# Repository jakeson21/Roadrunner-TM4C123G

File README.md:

# Roadrunner
Arduino clone based on TI's TM4C123G, an ARM M4F running at 80 MHz.

# Project Goal 
The goal of this project is to build a bridge between Texas Instrument's Tiva™ C LaunchPad, based on the TM4C123GH6PM, and the Arduino form factor. The LaunchPad series of development kits already benefit from an Arduino-like code development environment in the form of Energia, but lack a compatible form factor to make use of the extensive list of shields.

This project aims to merge these two worlds by putting the processing power and integrated peheripherial set of the 80-MHz ARM M4F based TM4C123 series of micro controllers into the Arduino-Leo (and Uno, Duemilanove, Due, *Mega) compatible form factor.
This will provide typical Arduino users with a much more powerful board while maintaining a familiar programming environment (through the use of Energia). It also provides a platform for those wanting to grow beyond this basic development approach into a more low-level IDE by using TI's free Code Composer Studio and selecting the EK-TM4C123GXL project configuration.

*The board breaks out all pins, but only utilizes the basic set of headers to maintain a 2" x 3" form factor.

# Other notable parameters
Most GPIO are 5V tolerant
Peripheral libraries are pre-loaded onto on-board ROM, reducing support code size.
32-bit CPU with single-precision FPU
Single-cycle multiply instruction and hardware divide
16-bit SIMD vector processing unit
Ultra-low power consumption with integrated sleep modes
etc... See datasheet for more information

# Project Planning
✔ Circuit design (using KiCAD). Programming will rely on the use of an EK-TM4C123GXL dev kit by tapping into its target ICDI JTAG headers.

✔ Board layout, including relocating Energia defined pins to their Arduino form factor locations.

✔ Fabrication (sent to OSH Park 4/16/2017)

✔ Board assembly

✔ Create custom board definition for use in Energia

▢ Hardware testing and verification

▢ Mass-production if enough people are interested

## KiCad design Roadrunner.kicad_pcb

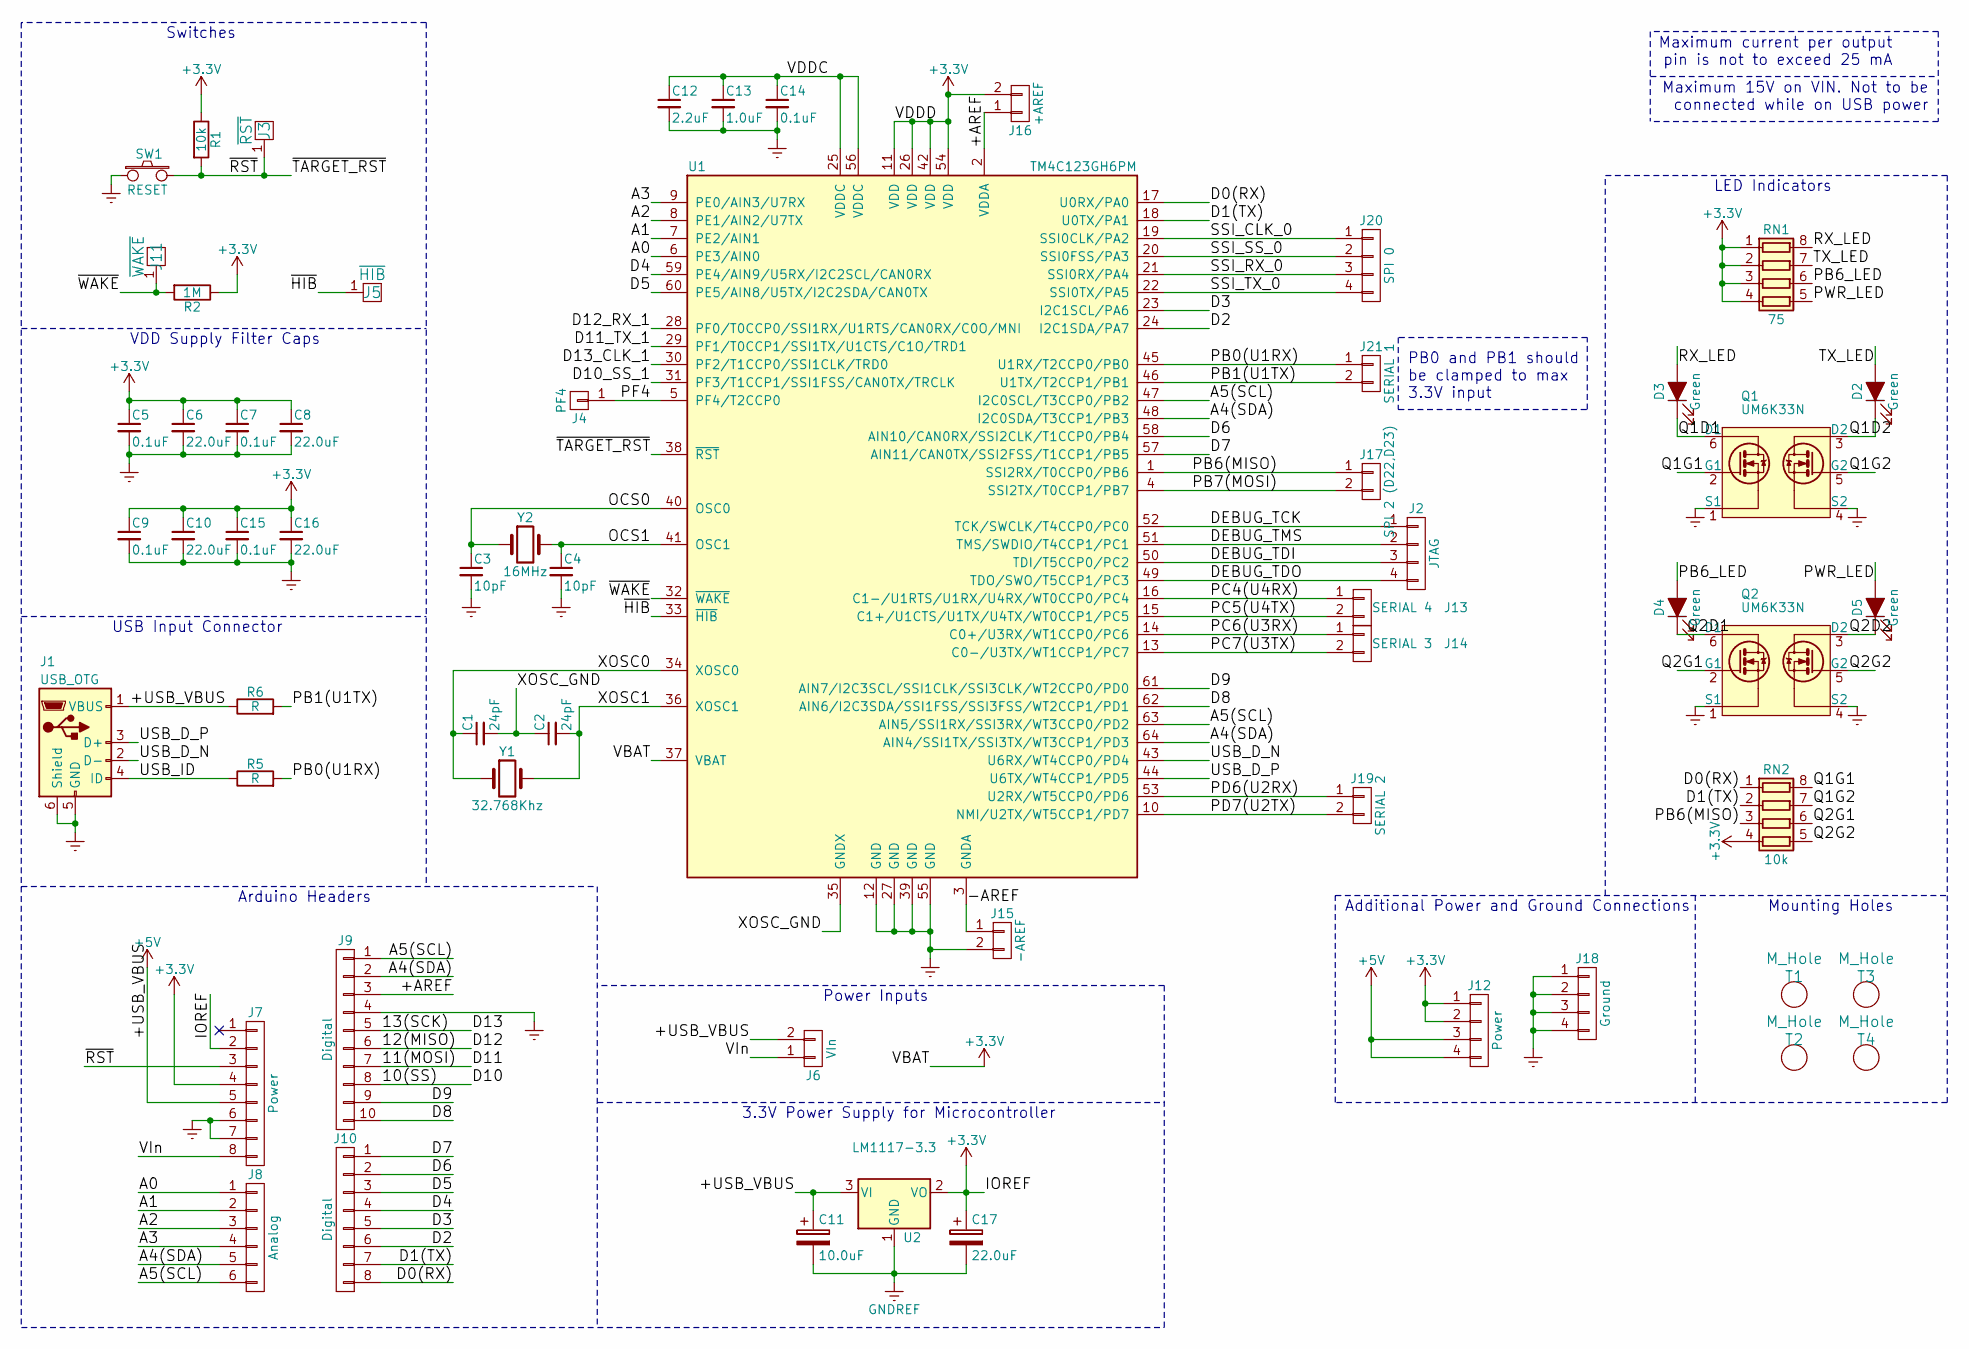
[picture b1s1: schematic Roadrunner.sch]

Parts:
C1, C2: 24pF; C_0603; Part # CC0603JRNPO9BN240
C3, C4: 10pF; C_0603; Part # C0603C100J5GACTU
C5, C7, C9, C14, C15: 0.1uF; C_0603; Part # CC0603JRX7R8BB104
C6, C8, C10, C16: 22.0uF; C_0805; Part # CL21A226MOCLRNC
C11: 10.0uF; C_0805
C12: 2.2uF; C_0603; Part # GRM188R61C225KE15D
C13: 1.0uF; C_0603; Part # GRM188R61C105KA93D
C17: 22.0uF; CP_Tantalum_Case-C_EIA-6032-28_Hand; Part # T491C226K016AT
D2, D3, D4, D5: Green; LED_0805; Part # LG R971-KN-1
J1: USB_OTG; USB_Micro_B_FCI_10118192; Part # 10118192-0001LF
J2: JTAG; Pin_Header_Straight_2x02_Pitch2.54mm
J3: ~RST; Pin_Header_Straight_1x01_Pitch2.54mm
J4: PF4; Socket_Strip_Straight_1x01_Pitch2.54mm
J5: ~HIB; Socket_Strip_Straight_1x01_Pitch2.54mm
J6: VIn; NetTie-I_Connected_SMD
J7: Power; Socket_Strip_Straight_1x08_Pitch2.54mm
J8: Analog; Socket_Strip_Straight_1x06_Pitch2.54mm
J9: Digital; Socket_Strip_Straight_1x10_Pitch2.54mm
J10: Digital; Socket_Strip_Straight_1x08_Pitch2.54mm
J11: ~WAKE; Socket_Strip_Straight_1x01_Pitch2.54mm
J12: Power; Socket_Strip_Straight_1x04_Pitch2.54mm
J13: SERIAL 4; Socket_Strip_Straight_1x02_Pitch2.54mm
J14: SERIAL 3; Socket_Strip_Straight_1x02_Pitch2.54mm
J15: -AREF; NetTie-I_Connected_SMD
J16: +AREF; NetTie-I_Connected_SMD
J17: SPI 2 (D22,D23); Socket_Strip_Straight_1x02_Pitch2.54mm
J18: Ground; Socket_Strip_Straight_1x04_Pitch2.54mm
J19: SERIAL 2; Socket_Strip_Straight_1x02_Pitch2.54mm
J20: SPI 0; Socket_Strip_Straight_2x02_Pitch2.54mm
J21: SERIAL 1; Socket_Strip_Straight_1x02_Pitch2.54mm
Q1, Q2: UM6K33N; SOT-363_SC-70-6; Part # UM6K33NTN
R1: 10k; R_0603_HandSoldering; Part # RC0603FR-0710KL
R2: 1M; R_0603_HandSoldering; Part # RCG06031M00FKEA
R5, R6: R; R_0805_HandSoldering
RN1: 75; YC164-JR-0775RL; Part # YC164-JR-0775RL
RN2: 10k; YC164-JR-0775RL; Part # EXB-38V103JV
SW1: RESET; SW_SPST_WS-TASV_4.5x4.5mm; Part # 430181038816
T1, T2, T3, T4: M_Hole; ArduinoMountingHole_3.2mm
U1: TM4C123GH6PM; LQFP-64_10x10mm_Pitch0.5mm; Part # TM4C123GH6PMI7
U2: LM1117-3.3; SOT-223; Part # LM1117IMPX-3.3/NOPB
Y1: 32.768Khz; Crystal_C26-LF_d2.1mm_l6.5mm_Horizontal_1EP_style1; Part # CFS-20632768HZFB
Y2: 16MHz; Crystal_SMD_5032-2pin_5.0x3.2mm_HandSoldering; Part # NX5032GA-16MHZ-STD-CSK-4

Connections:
+3V3: C5.1, C6.1, C7.1, C8.1, C9.1, C10.1, C15.1, C16.1, C17.1, J7.2, J7.4, J12.1, J12.2, J16.2, R1.1, R2.1, RN1.1 (R1.1), RN1.2 (R2.1), RN1.3 (R3.1), RN1.4 (R4.1), RN2.4 (R4.1), U1.11 (VDD), U1.26 (VDD), U1.37 (VBAT), U1.42 (VDD), U1.54 (VDD), U2.2 (VO)
+5V: C11.1, J1.1 (VBUS), J6.2, J7.5, J12.3, J12.4, R6.1, U2.3 (VI)
/10(SS): J9.8
/11(MOSI): J9.7
/12(MISO): J9.6
/13(SCK): J9.5
/+AREF: J9.3, J16.1, U1.2 (VDDA)
/-AREF: J15.1, U1.3 (GNDA)
/A0: J8.1, U1.6 (PE3/AIN0)
/A1: J8.2, U1.7 (PE2/AIN1)
/A2: J8.3, U1.8 (PE1/AIN2/U7TX)
/A3: J8.4, U1.9 (PE0/AIN3/U7RX)
/A4(SDA): J8.5, J9.2, U1.48 (I2C0SDA/T3CCP1/PB3), U1.64 (AIN4/SSI1TX/SSI3TX/WT3CCP1/PD3)
/A5(SCL): J8.6, J9.1, U1.47 (I2C0SCL/T3CCP0/PB2), U1.63 (AIN5/SSI1RX/SSI3RX/WT3CCP0/PD2)
/D0(RX): J10.8, RN2.1 (R1.1), U1.17 (U0RX/PA0)
/D1(TX): J10.7, RN2.2 (R2.1), U1.18 (U0TX/PA1)
/D2: J10.6, U1.24 (I2C1SDA/PA7)
/D3: J10.5, U1.23 (I2C1SCL/PA6)
/D4: J10.4, U1.59 (PE4/AIN9/U5RX/I2C2SCL/CAN0RX)
/D5: J10.3, U1.60 (PE5/AIN8/U5TX/I2C2SDA/CAN0TX)
/D6: J10.2, U1.58 (AIN10/CAN0RX/SSI2CLK/T1CCP0/PB4)
/D7: J10.1, U1.57 (AIN11/CAN0TX/SSI2FSS/T1CCP1/PB5)
/D8: J9.10, U1.62 (AIN6/I2C3SDA/SSI1FSS/SSI3FSS/WT2CCP1/PD1)
/D9: J9.9, U1.61 (AIN7/I2C3SCL/SSI1CLK/SSI3CLK/WT2CCP0/PD0)
/D10_SS_1: U1.31 (PF3/T1CCP1/SSI1FSS/CAN0TX/TRCLK)
/D11_TX_1: U1.29 (PF1/T0CCP1/SSI1TX/U1CTS/C1O/TRD1)
/D12_RX_1: U1.28 (PF0/T0CCP0/SSI1RX/U1RTS/CAN0RX/C0O/MNI)
/D13_CLK_1: U1.30 (PF2/T1CCP0/SSI1CLK/TRD0)
/DEBUG_TCK: J2.1, U1.52 (TCK/SWCLK/T4CCP0/PC0)
/DEBUG_TDI: J2.3, U1.50 (TDI/T5CCP0/PC2)
/DEBUG_TDO: J2.4, U1.49 (TDO/SWO/T5CCP1/PC3)
/DEBUG_TMS: J2.2, U1.51 (TMS/SWDIO/T4CCP1/PC1)
/OCS0: C3.1, U1.40 (OSC0), Y2.1
/OCS1: C4.1, U1.41 (OSC1), Y2.2
/PB0(U1RX): J21.1, R5.2, U1.45 (U1RX/T2CCP0/PB0)
/PB1(U1TX): J21.2, R6.2, U1.46 (U1TX/T2CCP1/PB1)
/PB6(MISO): J17.1, RN2.3 (R3.1), U1.1 (SSI2RX/T0CCP0/PB6)
/PB6_LED: D4.2 (A), RN1.6 (R3.2)
/PB7(MOSI): J17.2, U1.4 (SSI2TX/T0CCP1/PB7)
/PC4(U4RX): J13.1, U1.16 (C1-/U1RTS/U1RX/U4RX/WT0CCP0/PC4)
/PC5(U4TX): J13.2, U1.15 (C1+/U1CTS/U1TX/U4TX/WT0CCP1/PC5)
/PC6(U3RX): J14.1, U1.14 (C0+/U3RX/WT1CCP0/PC6)
/PC7(U3TX): J14.2, U1.13 (C0-/U3TX/WT1CCP1/PC7)
/PD6(U2RX): J19.1, U1.53 (U2RX/WT5CCP0/PD6)
/PD7(U2TX): J19.2, U1.10 (NMI/U2TX/WT5CCP1/PD7)
/PF4: J4.1, U1.5 (PF4/T2CCP0)
/PWR_LED: D5.2 (A), RN1.5 (R4.2)
/Q1D1: D3.1 (K), Q1.6 (D1)
/Q1D2: D2.1 (K), Q1.3 (D2)
/Q1G1: Q1.2 (G1), RN2.8 (R1.2)
/Q1G2: Q1.5 (G2), RN2.7 (R2.2)
/Q2D1: D4.1 (K), Q2.6 (D1)
/Q2D2: D5.1 (K), Q2.3 (D2)
/Q2G1: Q2.2 (G1), RN2.6 (R3.2)
/Q2G2: Q2.5 (G2), RN2.5 (R4.2)
/RX_LED: D3.2 (A), RN1.8 (R1.2)
/SSI_CLK_0: J20.1, U1.19 (SSI0CLK/PA2)
/SSI_RX_0: J20.3, U1.21 (SSI0RX/PA4)
/SSI_SS_0: J20.2, U1.20 (SSI0FSS/PA3)
/SSI_TX_0: J20.4, U1.22 (SSI0TX/PA5)
/TX_LED: D2.2 (A), RN1.7 (R2.2)
/USB_D_N: J1.2 (D-), U1.43 (U6RX/WT4CCP0/PD4)
/USB_D_P: J1.3 (D+), U1.44 (U6TX/WT4CCP1/PD5)
/USB_ID: J1.4 (ID), R5.1
/VDDC: C12.1, C13.1, C14.1, U1.25 (VDDC), U1.56 (VDDC)
/VIn: J6.1, J7.8
/XOSC0: C1.1, U1.34 (XOSC0), Y1.1
/XOSC1: C2.2, U1.36 (XOSC1), Y1.2
/XOSC_GND: C1.2, C2.1, U1.35 (GNDX)
/~HIB: J5.1, U1.33 (~HIB~)
/~RST: J3.1, J7.3, R1.2, SW1.2, U1.38 (~RST~)
/~WAKE: J11.1, R2.2, U1.32 (~WAKE~)
GNDREF: C3.2, C4.2, C5.2, C6.2, C7.2, C8.2, C9.2, C10.2, C11.2, C12.2, C13.2, C14.2, C15.2, C16.2, C17.2, J1.5 (GND), J1.6 (Shield), J7.6, J7.7, J9.4, J15.2, J18.1, J18.2, J18.3, J18.4, Q1.1 (S1), Q1.4 (S2), Q2.1 (S1), Q2.4 (S2), SW1.1, U1.12 (GND), U1.27 (GND), U1.39 (GND), U1.55 (GND), U2.1 (GND)

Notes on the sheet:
PB0 and PB1 should be clamped to max 3.3V input
Maximum current per output pin is not to exceed 25 mA
Maximum 15V on VIN. Not to be connected while on USB power
LED Indicators
Additional Power and Ground Connections
Mounting Holes
Arduino Headers
3.3V Power Supply for Microcontroller
Switches
USB Input Connector
Power Inputs
VDD Supply Filter Caps

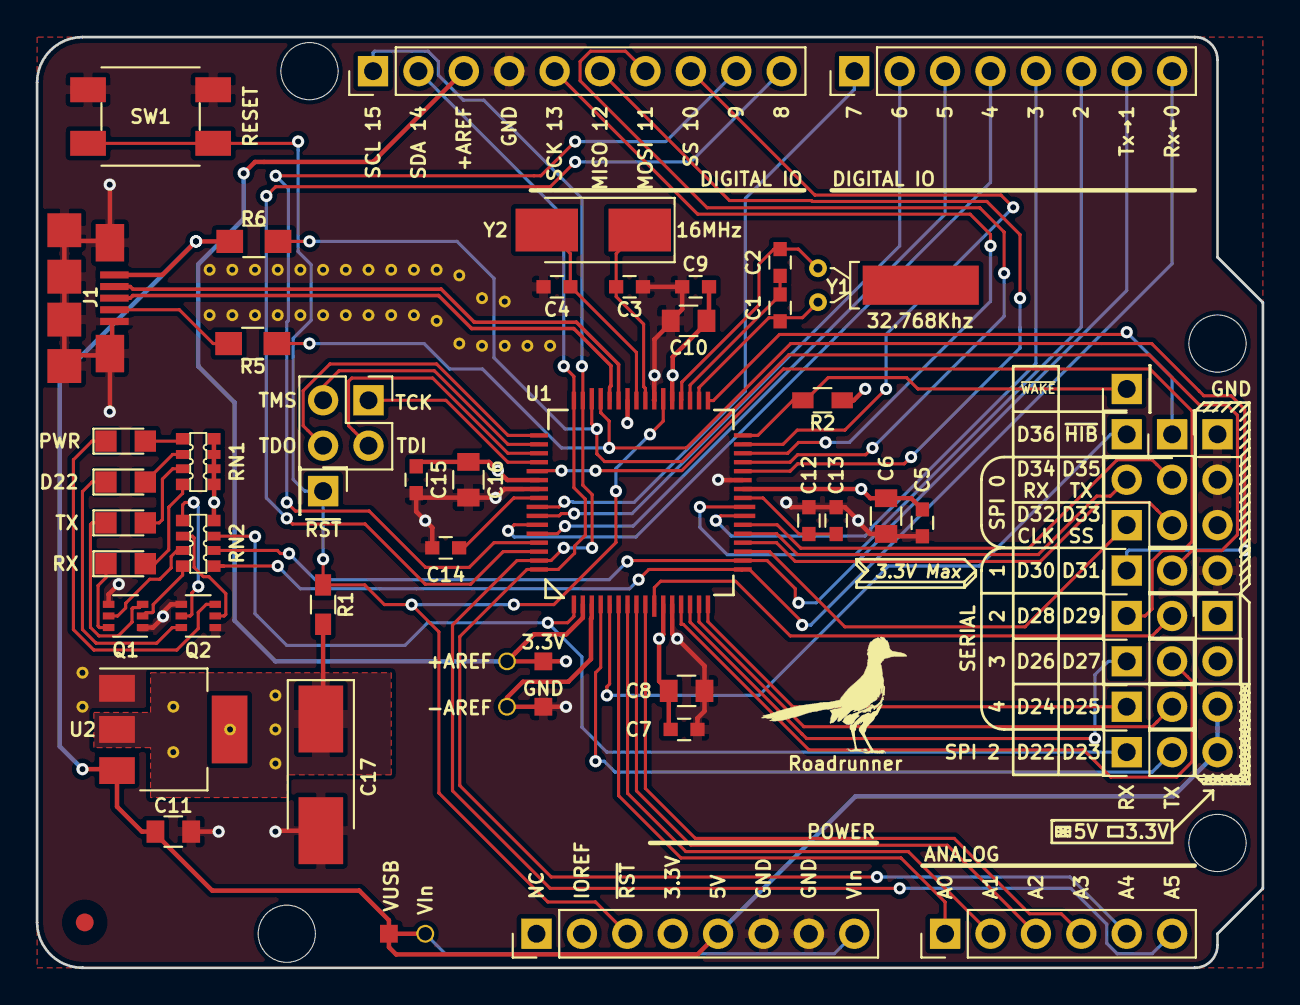
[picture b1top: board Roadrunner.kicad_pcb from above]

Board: 4 copper layers, 68.6 x 52.1 mm, 61 parts (0 on the bottom side), 65 nets.

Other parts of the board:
RoadrunnerLogoMedium: G***; RoadrunnerLogoMedium
RoadrunnerLogoSmall: G***; RoadrunnerLogoSmall

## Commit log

2017-04-17 Version 1.0 - Sent to OSH Park 4/16/2017
2017-04-17 Added as-built Mfg. part numbers and full descriptions to each component.
2017-04-19 Added KiCAD silkscreen and name to top layer
2017-05-06 Fixed issue with incorrect schematic symbol and footprint for 3.3V regulator IC. Fixed typo in path
2017-05-06 Adding images and renders
2017-05-09 Fixed "Swap UART Labels on D0,D1 #7"
    Had U0Tx and U0Rx labled incorrectly in schematic.
    Fixed labels and rerouted signals to correct pins.
2017-05-09 Modified LEGO mounting hole - Increased width by 0.05 mm - Removed through hole plating (now NPTH)
2017-07-22 Major changes to board layout and design leading towards revisoin v1.1
2017-07-30 Recent modifications to layout. Switching to resistor arrays. Adding Roadrunner image.
2017-07-30 Removing unneeded file
2017-08-15 Renaming project ro Roadrunner
    Also include various routing changes and a new logo
2017-08-15 Added additional 3.3V x4 and GND x4 headers to rear of board
2019-01-09 Sweeping changes to board layout.
2019-01-09 Swapped some 3.3v outputs on rear header for 5V.
